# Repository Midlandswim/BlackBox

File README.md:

# BlackBox
BlackBox Flight Data Recorder

This is in partnership with Dhalwani Designs, which holds all rights, data, and procedures for this project and the related. This project was made for the Buckeye Space Launch Initiative Liquids Research Team. <br />

Researcher: Wilson Dhalwani <br />
Aides: Mr. Julian Hooks (OSU) <br />
Context: Dhalwani Designs Sanctioned Project and BSLI Liquids Project <br />
Project Name: The Blackbox <br />
Start Date: January 09, 2025 <br /> 

The following repository is for documenting and sharing my work in this research and competition project and its related fields of electrical and avionics engineering. This was also made to record my process of solving the issue at hand so that others can learn and build upon my work. Wanting to advance my experience and skills in avionics, as well as PCB design, I sought to join the Buckeye Space Launch Initiative, and specifically the Liquids Project Team (https://www.bsli.space/projects/liquids/). I quickly grasped concepts and joined the electronics/avionics subteam. Working closely with Mr. Julian Hooks, I have gained great experience, expertise, and knowledge in the field and its accompanying areas of study/research. Mr. Hooks has been an amazing team lead, mentor, and friend, and I hope to grow into half the leader and engineer he is. I was quickly assigned the task of creating the dedicated and versatile flight data recorder for the entire system of our up and coming rocket. For some context, this rocket will be a high powered rocket that aims to break the current collegiete apogee record. All custom designed, built, and manufactured, this rocket is composed of comepletly novel and innovative approaches to existing technology to advance the capabilities of the field but to also promote increased investment/interest into the related fields. Getting back to my individual role and contributions, I solely worked on the research, design, and development of this board, ensuring this critical component of the entire electronic as well as non-electronic systems would not only do its duty as our last resort, but still aid in achieving the overarching goals. One may notice key design choices throughout this board, as well as its expansive (and further expandable) capabilities. Ranging from dedicated and secure communication lines to extremely sensitive sensors, the BlackBox, as I have named it, will be a reliable yet hopefully unused aspect of this rocket. Aside from the more standard features such as event/data recording and reliable dedicated power systems, the processing and versatility of this system have been unmatched thus far (as compared to similar models in the collegeite field). A specialized enclosure was also designed to aid in protecting the board while also maximizing utility and accessibility during the implementation phase. This project has no end date as an innovation never ends, rather, continues until the idea is forgotten, and my hope is that this work can be the basis for future engineers who, too, find great excitement in innovation and design. <br />

Should you have any questions, comments, or just wish to reach out, email me at wilson.dhalwani@gmail.com !

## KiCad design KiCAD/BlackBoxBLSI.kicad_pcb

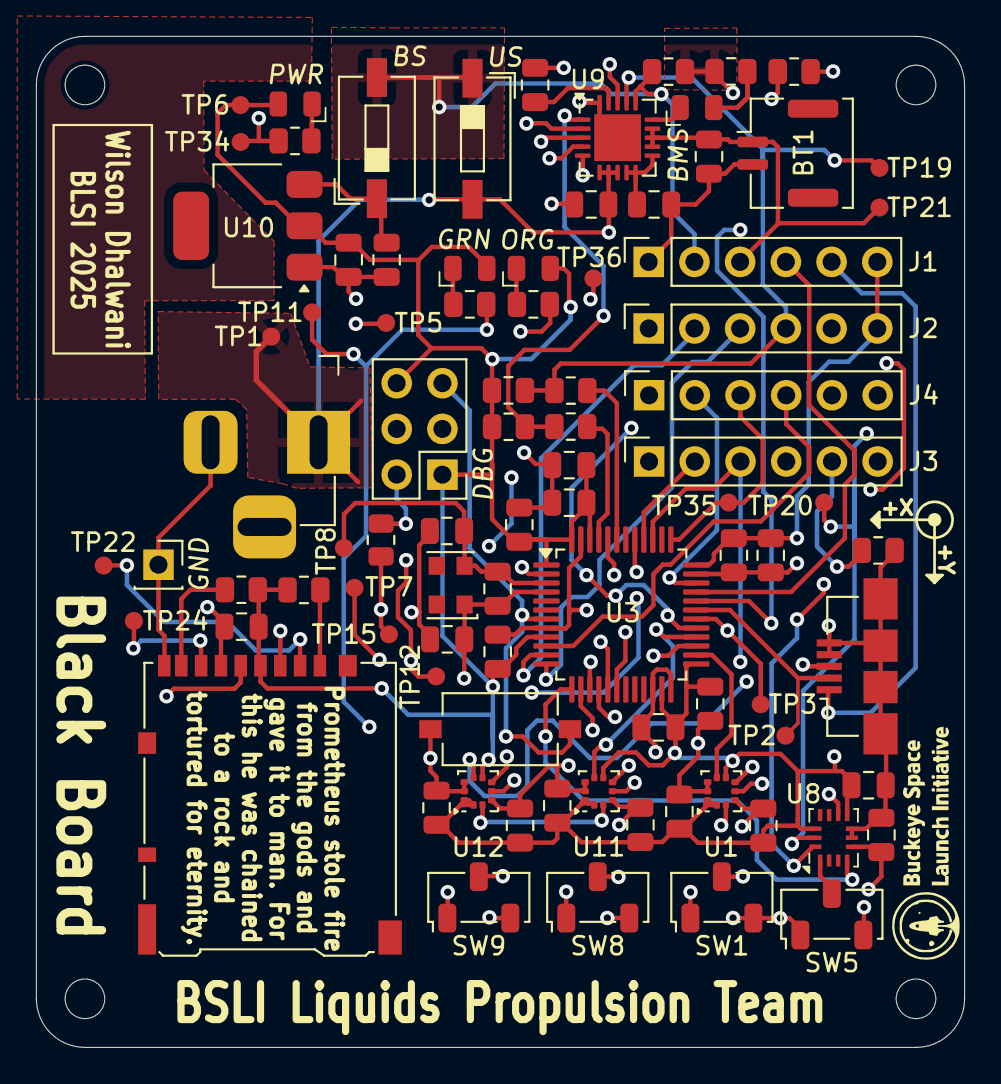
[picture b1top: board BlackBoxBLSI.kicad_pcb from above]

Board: 4 copper layers, 51.6 x 56.2 mm, 91 parts (0 on the bottom side), 52 nets.

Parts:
BMS: REDLED; LED_0805_2012Metric
BS: SW_SPST; SW_DIP_SPSTx01_Slide_6.7x4.1mm_W6.73mm_P2.54mm_LowProfile_J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
BT1: 4.2V Batt; Molex_CLIK-Mate_502382-0270_1x02-1MP_P1.25mm_Vertical
C1, C2, C43, C44, C45, C46: 100nF; C_0805_2012Metric
C5, C12, C37, C40, C41: 10 uF; C_0805_2012Metric
C6, C7, C8, C9, C10, C11, C34, C35, C36, C42: 100 nF; C_0805_2012Metric
C13, C14: 0.1 uF; C_0805_2012Metric
C15: 3 pF; C_0805_2012Metric
C38, C39: 22 uF; C_0805_2012Metric
DBG: Conn_02x03_Counter_Clockwise; PinHeader_2x03_P2.54mm_Vertical
GND: Conn_01x01_Pin; PinSocket_1x01_P2.54mm_Vertical
GRN: GREENLED; LED_0805_2012Metric
H1, H2, H3, H4: MountingHole_Pad; MountingHole_2.2mm_M2_ISO7380
J1, J2, J3, J4: Conn_01x06_Pin; PinSocket_1x06_P2.54mm_Vertical
J6: Barrel_Jack; BarrelJack_Horizontal
J8: USB_B_Micro; USB_Micro-B_Amphenol_10104110_Horizontal
J9: Micro_SD_Card; microSD_HC_Hirose_DM3AT-SF-PEJM5
LEDRES1, LEDRES2: 270Ω; R_0805_2012Metric
LEDRES3: 75Ω; R_0805_2012Metric
ORG: ORNGELED; LED_0805_2012Metric
PWR: BLULED; LED_0805_2012Metric
R6, R7: 4.7kΩ; R_0805_2012Metric
R8, R9: 1Ω; R_0805_2012Metric
R18, R20: 10 kΩ; R_0805_2012Metric
R19: 270 Ω; R_0805_2012Metric
R21: 10kΩ; R_0805_2012Metric
R22, R23: 10k; R_0805_2012Metric
RSTCAP1: 0.1uF; R_0805_2012Metric
SW1, SW5, SW8, SW9: SW_SPDT; Nidec_Copal_CAS-120A
SW6: SW_Push; SW_Tactile_SPST_NO_Straight_CK_PTS636Sx25SMTRLFS
TP1, TP2, TP3, TP5, TP6, TP7, TP8, TP11, TP12, TP15, TP19, TP20, TP21, TP22, TP24, TP34, TP35, TP36: TestPoint; TestPoint_Pad_D1.0mm
U1, U11, U12: BMP390; ST_HLGA-10_2x2mm_P0.5mm_LayoutBorder3x2y
U3: STM32U575CIT6; LQFP-48_7x7mm_P0.5mm
U8: BMI323; Bosch_LGA-14_3x2.5mm_P0.5mm
U9: ADP5063; LFCSP-20-1EP_4x4mm_P0.5mm_EP2.6x2.6mm
U10: AMS1117-3.3; SOT-223
US: SW_SPST; SW_DIP_SPSTx01_Slide_6.7x4.1mm_W6.73mm_P2.54mm_LowProfile_J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
Y1: Crystal 32.768 kHz; Oscillator_SMD_EuroQuartz_XO32-4Pin_3.2x2.5mm

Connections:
+3V3: C1.2, C2.1, C5.1, C6.1, C7.1, C8.1, C9.1, C10.1, C11.1, C12.1, C34.1, C35.1, C41.1, C42.2, C43.1, C44.2, C45.1, C46.2, DBG.1, DBG.6, GRN.2 (A), J1.6, J2.6, J9.4 (VDD), ORG.2 (A), PWR.2 (A), R6.1, R7.2, R19.2, R20.2, R22.1, R23.1, SW1.3 (C), SW5.1 (A), SW8.3 (C), SW9.3 (C), TP6.1, U1.1 (VDDIO), U1.6 (CSB), U1.10 (VDD), U3.1 (VBAT), U3.9 (VDDA), U3.23 (VDD11), U3.25 (VDD), U3.36 (VDD), U3.46 (VDD11), U3.48 (VDD), U8.5 (VDDIO), U8.8 (VDD), U8.12 (CSB), U10.2 (VO), U11.1 (VDDIO), U11.6 (CSB), U11.10 (VDD), U12.1 (VDDIO), U12.6 (CSB), U12.10 (VDD)
+5V: C37.2, J1.5, J6.1, J8.1 (VBUS), TP1.1, U9.6 (VINx), U9.7 (VINx), U9.8 (VINx), US.2 (B)
/BATSNS: BT1.1 (+), C39.2, J1.3, TP21.1, U9.4 (BAT_SNS), U9.12 (ISO_Bx), U9.13 (ISO_Bx), U9.14 (ISO_Bx)
/BOOT0: J3.6, R21.2, TP15.1, U3.44 (PH3)
/Debug_SWCLK: J4.3, TP35.1, U3.37 (PA14)
/Debug_SWDIO: J4.2, TP36.1, U3.34 (PA13)
/GPIO10: J4.4, U3.10 (PA0)
/GPIO13: J4.5, U3.2 (PC13)
/GPIO15: J4.6, U3.15 (PA5)
/GPIO_BMS1: U3.29 (PA8), U9.5 (D_IO1)
/GPIO_BMS2: U3.32 (PA11), U9.3 (D_IO2)
/GPIO_BMS3: J1.4, U3.33 (PA12), U9.2 (D_IO3)
/INT1_BMI: U3.13 (PA3), U8.4 (INT1)
/INT2_BMI: U3.14 (PA4), U8.9 (INT2)
/INT_BMP1: U1.7 (INT), U3.26 (PB13)
/INT_BMP2: U3.27 (PB14), U12.7 (INT)
/INT_BMP3: U3.28 (PB15), U11.7 (INT)
/LED_GRN: LEDRES1.2, TP11.1, U3.16 (PA6)
/LED_RED: LEDRES2.2, TP12.1, U3.17 (PA7)
/NRST: DBG.5, J3.5, RSTCAP1.2, SW6.1, TP5.1, U3.7 (NRST)
/OSC32IN: C13.1, C15.1, TP8.1, U3.3 (PC14), Y1.2
/OSC32OUT: C14.2, C15.2, TP7.1, U3.4 (PC15), Y1.1
/SCL: J2.5, R7.1, R9.1, TP20.1, U1.2 (SCK), U8.13 (SCx), U9.1 (SCL), U11.2 (SCK), U12.2 (SCK)
/SDA: J2.4, R6.2, R8.1, TP19.1, U1.4 (SDI), U8.14 (SDx), U9.17 (SDA), U11.4 (SDI), U12.4 (SDI)
/SPI_SDCARD_CS: J9.2 (DAT3/CD), TP22.1, U3.18 (PB0)
/SPI_SDCARD_MISO: J3.2, J9.7 (DAT0), TP24.1, U3.40 (PB4)
/SPI_SDCARD_MOSI: J3.4, J9.3 (CMD), U3.41 (PB5)
/SPI_SDCARD_SCK: J3.3, J9.5 (CLK), U3.39 (PB3)
/SYS_LOAD: BS.2 (B), J1.2, R20.1, U9.16 (SYS_EN), US.1 (A)
/UART_RX: J2.2, U3.11 (PA1)
/UART_TX: J2.3, U3.12 (PA2)
/USB_D+: J8.3 (D+), TP3.1, U3.30 (PA9)
/USB_D-: J8.2 (D-), TP2.1, U3.31 (PA10)
GND: BT1.2 (-), C1.1, C2.2, C5.2, C6.2, C7.2, C8.2, C9.2, C10.2, C11.2, C12.2, C13.2, C14.1, C34.2, C35.2, C36.1, C37.1, C38.1, C39.1, C40.2, C41.2, C42.1, C43.2, C44.1, C45.2, C46.1, DBG.3, DBG.4, GND.1, J1.1, J2.1, J3.1, J4.1, J6.2, J8.4 (ID), J8.5 (GND), J8.6 (Shield), J9.6 (VSS), J9.9 (SHIELD), LEDRES3.2, R18.2, RSTCAP1.1, SW1.1 (A), SW5.3 (C), SW6.2, SW8.1 (A), SW9.1 (A), TP34.1, U1.3 (VSS), U1.8 (VSS), U1.9 (VSS), U3.8 (VSSA), U3.22 (VSSSMPS), U3.24 (VSS), U3.35 (VSS), U3.47 (VSS), U8.6 (GNDIO), U8.7 (GND), U9.20 (GND), U9.21 (EP), U10.1 (GND), U11.3 (VSS), U11.8 (VSS), U11.9 (VSS), U12.3 (VSS), U12.8 (VSS), U12.9 (VSS)
unnamed: C38.2, U9.9 (ISO_Sx), U9.10 (ISO_Sx), U9.11 (ISO_Sx)
unnamed: GRN.1 (K), LEDRES1.1
unnamed: LEDRES2.1, ORG.1 (K)
unnamed: BMS.2 (A), R19.1
unnamed: BMS.1 (K), U9.15 (ILED)
unnamed: LEDRES3.1, PWR.1 (K)
unnamed: DBG.2, R21.1
unnamed: J9.8 (DAT1), R22.2
unnamed: J9.1 (DAT2), R23.2
unnamed: SW1.2 (B), U1.5 (SDO)
unnamed: BS.1 (A), C40.1, U10.3 (VI)
unnamed: SW5.2 (B), U8.1 (SDO)
unnamed: SW8.2 (B), U11.5 (SDO)
unnamed: SW9.2 (B), U12.5 (SDO)
unnamed: R8.2, U3.43 (PB7)
unnamed: R9.2, U3.45 (PB8)
unnamed: C36.2, U9.19 (CBP)
unnamed: R18.1, U9.18 (THR)

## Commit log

2025-07-24 Relevant KiCAD Files
    All KiCAD files for now
2025-07-24 Complete KiCAD Schematic
    Schematic with Heirachy
2025-07-24 Miscellanous Stuff
    Netlist and BOM?
2025-07-24 PCB Render Images
    Board Render Images from KiCAD
